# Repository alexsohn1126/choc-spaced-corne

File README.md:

# choc-spaced-corne
Choc spaced corne based on klouderone's [cornev4promicroedition](https://github.com/klouderone/cornev4promicroedition)

Does not feature hotswap and TRRS plugs.

Pinouts are the same as the classic corne, so the firmware setup is as simple as choosing corne in [zmk setup](https://zmk.dev/docs/user-setup).

## Images

## Materials Used & Costs
| Material                                                                                                         | Cost    |
|------------------------------------------------------------------------------------------------------------------|---------|
| [Choc v1 pink switches 50 pcs](https://www.aliexpress.us/item/3256804880270570.html)                             | ~30 USD |
| [100pcs SMD diodes](https://www.aliexpress.us/item/3256803008359866.html)                                        | ~1 USD  |
| [100pcs silicone feet](https://www.aliexpress.us/item/3256802433629049.html)                                     | ~1 USD  |
| [Black choc keycaps 50pcs + 2 of 1.5u keycap](https://www.boardsource.xyz/products/MBK_blanks)                   | ~20 USD |
| 2 of [SuperMini NRF52840](https://www.aliexpress.us/item/3256805848952479.html)                                  | ~10 USD |
| [10pcs 301230 batteries](https://www.aliexpress.us/item/3256806816440012.html)                                   | ~8 USD  |
| 5mm version of [copper m2 copper pillar](https://www.aliexpress.us/item/3256804637215652.html)                   | ~3 USD  |
| 4mm version of [m2 screws](https://www.aliexpress.us/item/3256804698330962.html)                                 | ~1 USD  |
| 2 of [nice!view](https://typeractive.xyz/products/nice-view)                                                     | ~40 USD |
| 2 of [PCM12SMTR](https://www.digikey.com/en/products/detail/c-k/pcm12smtr/1640112)                               | ~3 USD  |
| 2 of [EVQ-P7A01P](https://www.digikey.com/en/products/detail/panasonic-electronic-components/evq-p7a01p/4429447) | ~1 USD  |
| pcb order at jlcpcb                                                                                              | ~30 USD |
| Optional: [pvc washers](https://www.aliexpress.us/item/3256804190495486.html)                                    | ~2 USD  |
|                                                                                                                  |         |
| Total                                                                                                            | 150 USD |

After I did the calculations, this isn't much cheaper than getting a kit from vendors out there after shipping, just as a warning.

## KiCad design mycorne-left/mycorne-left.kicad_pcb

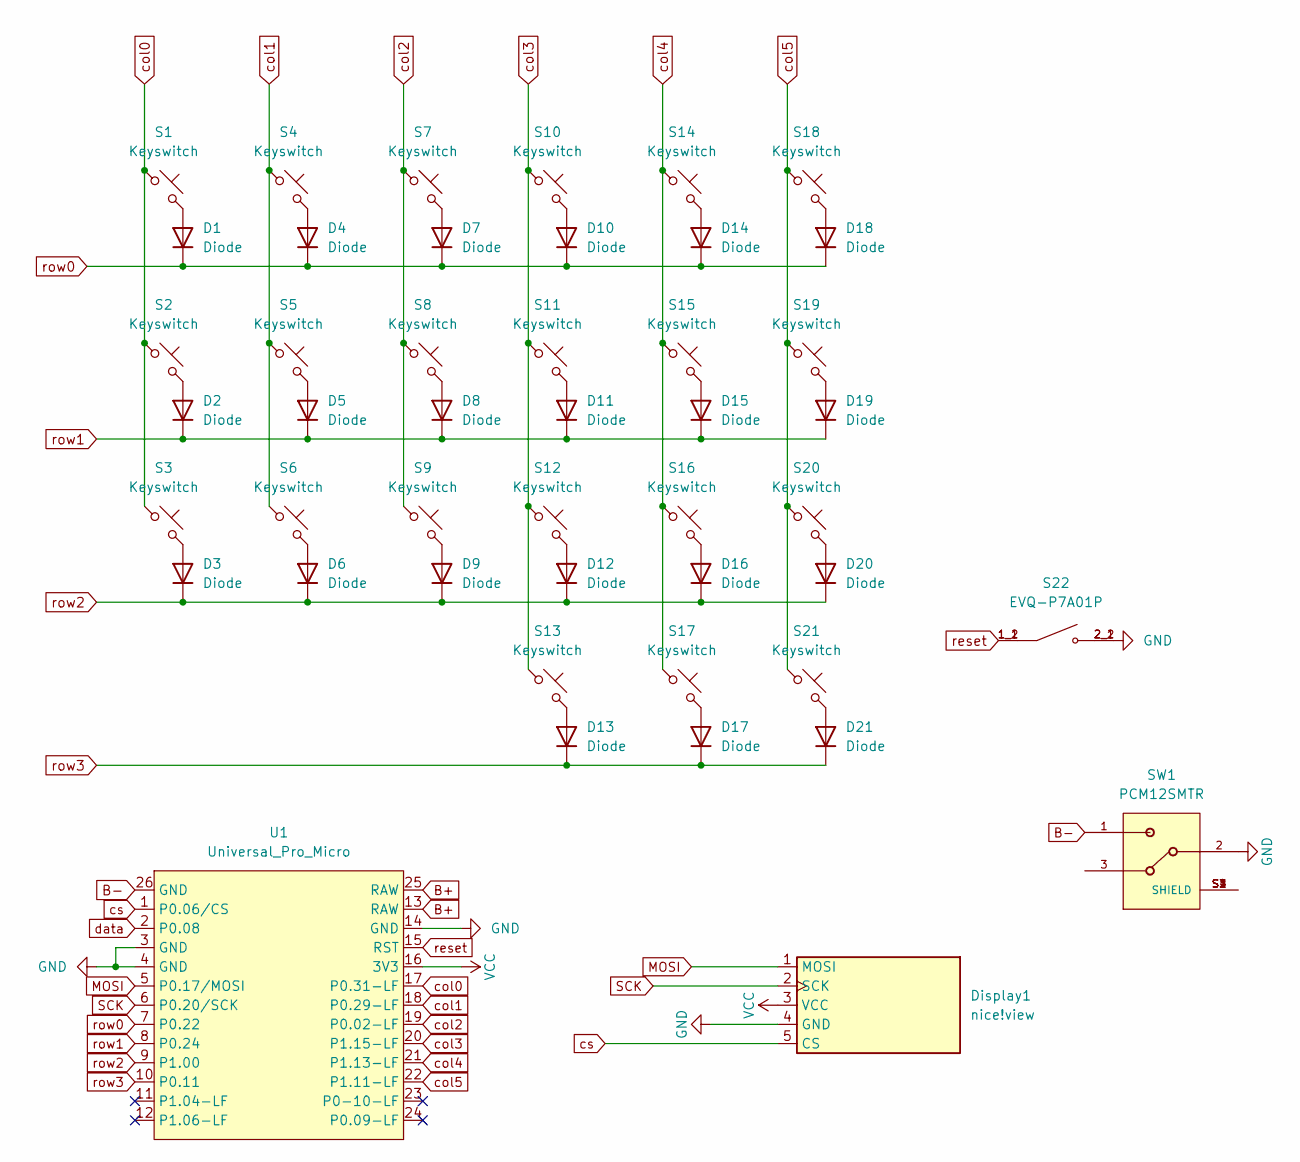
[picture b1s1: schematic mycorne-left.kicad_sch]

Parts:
D1, D2, D3, D4, D5, D6, D7, D8, D9, D10, D11, D12, D13, D14, D15, D16, D17, D18, D19, D20, D21: Diode; Diode_SOD-123
Display1: nice!view; nice_view
S1, S2, S3, S4, S5, S6, S7, S8, S9, S10, S11, S12, S13, S14, S15, S16, S17, S18, S19, S20: Keyswitch; Choc_V1_1.00u
S21: Keyswitch; Choc_V1_1.50u
S22: EVQ-P7A01P; SW_EVQ-P7A01P; PARTREV 2022.4
SW1: PCM12SMTR; SW_SPDT_PCM12
U1: Universal_Pro_Micro; Universal_Pro_Micro_Footprint

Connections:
B+: U1.13 (RAW), U1.25 (RAW)
B-: SW1.1, U1.26 (GND)
GND: Display1.4 (GND), S22.2_1, S22.2_2, SW1.2, U1.3 (GND), U1.4 (GND), U1.14 (GND)
MOSI: Display1.1 (MOSI), U1.5 (P0.17/MOSI)
unnamed: D1.2 (A), S1.2
unnamed: D2.2 (A), S2.2
unnamed: D3.2 (A), S3.2
unnamed: D4.2 (A), S4.2
unnamed: D5.2 (A), S5.2
unnamed: D6.2 (A), S6.2
unnamed: D7.2 (A), S7.2
unnamed: D8.2 (A), S8.2
unnamed: D9.2 (A), S9.2
unnamed: D10.2 (A), S10.2
unnamed: D11.2 (A), S11.2
unnamed: D12.2 (A), S12.2
unnamed: D13.2 (A), S13.2
unnamed: D14.2 (A), S14.2
unnamed: D15.2 (A), S15.2
unnamed: D16.2 (A), S16.2
unnamed: D17.2 (A), S17.2
unnamed: D18.2 (A), S18.2
unnamed: D19.2 (A), S19.2
unnamed: D20.2 (A), S20.2
unnamed: D21.2 (A), S21.2
SCK: Display1.2 (SCK), U1.6 (P0.20/SCK)
VCC: Display1.3 (VCC), U1.16 (3V3)
col0: S1.1, S2.1, S3.1, U1.17 (P0.31-LF)
col1: S4.1, S5.1, S6.1, U1.18 (P0.29-LF)
col2: S7.1, S8.1, S9.1, U1.19 (P0.02-LF)
col3: S10.1, S11.1, S12.1, S13.1, U1.20 (P1.15-LF)
col4: S14.1, S15.1, S16.1, S17.1, U1.21 (P1.13-LF)
col5: S18.1, S19.1, S20.1, S21.1, U1.22 (P1.11-LF)
cs: Display1.5 (CS), U1.1 (P0.06/CS)
data: U1.2 (P0.08)
reset: S22.1_1, S22.1_2, U1.15 (RST)
row0: D1.1 (K), D4.1 (K), D7.1 (K), D10.1 (K), D14.1 (K), D18.1 (K), U1.7 (P0.22)
row1: D2.1 (K), D5.1 (K), D8.1 (K), D11.1 (K), D15.1 (K), D19.1 (K), U1.8 (P0.24)
row2: D3.1 (K), D6.1 (K), D9.1 (K), D12.1 (K), D16.1 (K), D20.1 (K), U1.9 (P1.00)
row3: D13.1 (K), D17.1 (K), D21.1 (K), U1.10 (P0.11)

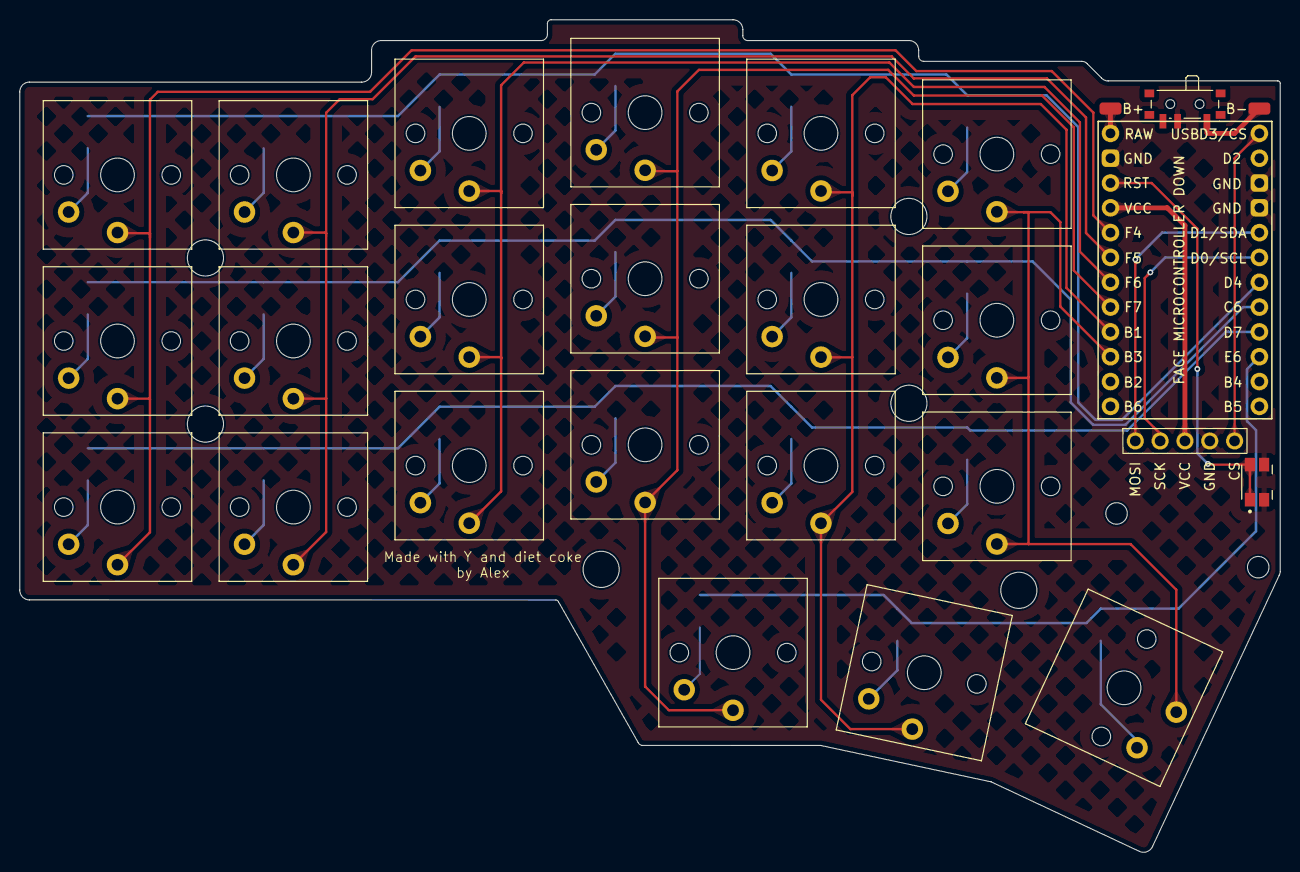
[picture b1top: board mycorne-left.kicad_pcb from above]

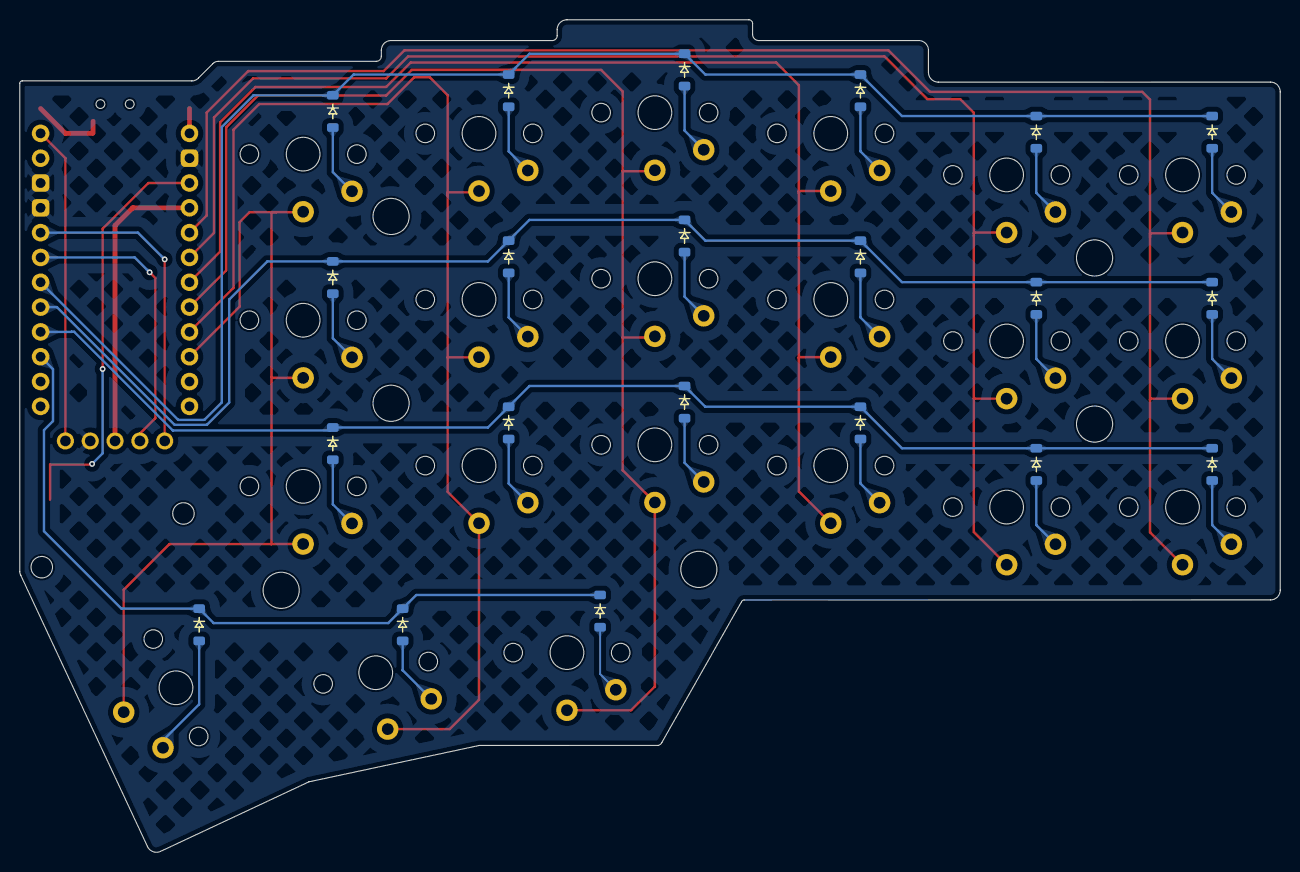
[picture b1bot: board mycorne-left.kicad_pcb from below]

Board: 2 copper layers, 129.0 x 85.2 mm, 46 parts (21 on the bottom side), 39 nets.

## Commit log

2024-09-02 added pcb files to the repo
2024-09-02 add images
2024-09-02 add images to readme
2024-09-06 Add materials costs to the readme
